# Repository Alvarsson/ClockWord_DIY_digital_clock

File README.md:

# ClockWork_DIY_digital_clock
Code for homemade digital clock. 

# Effects to add
"Circle" + line in the middle
Fill in/out on number change
"Circle" wave

# Important notes
The KiCad design doesn't have a voltage divider for the TX pin of the ESP8266. If the arduino isn't talking to the ESP8266 properly, make sure that the input voltage to the Arduino isn't too high.

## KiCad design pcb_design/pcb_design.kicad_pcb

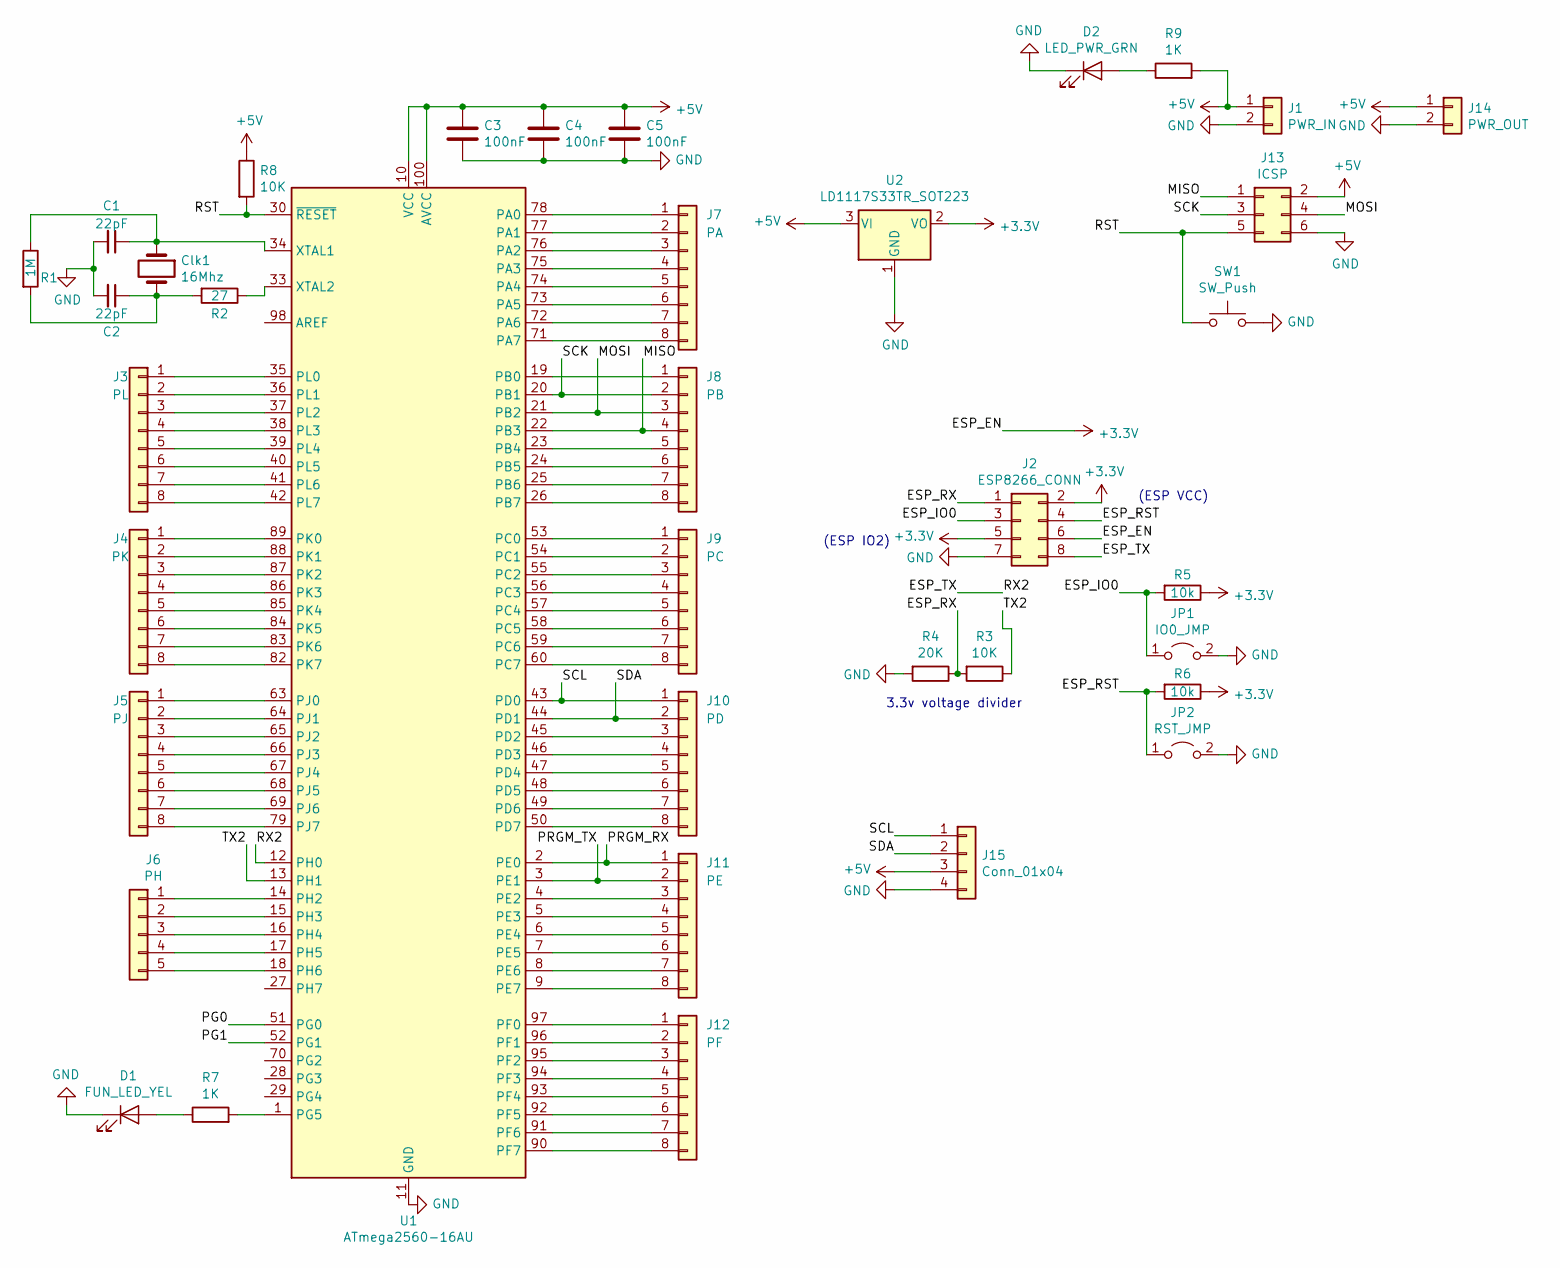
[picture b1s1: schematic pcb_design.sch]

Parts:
C1, C2: 22pF; C_0603_1608Metric
C3, C4, C5: 100nF; C_0603_1608Metric
Clk1: 16Mhz; Crystal_HC49-4H_Vertical
D1: FUN_LED_YEL; LED_0603_1608Metric
D2: LED_PWR_GRN; LED_0603_1608Metric
J1: PWR_IN; PinHeader_1x02_P2.54mm_Vertical
J2: ESP8266_CONN; PinHeader_2x04_P2.54mm_Vertical
J3: PL; PinHeader_1x08_P2.54mm_Vertical
J4: PK; PinHeader_1x08_P2.54mm_Vertical
J5: PJ; PinHeader_1x08_P2.54mm_Vertical
J6: PH; PinHeader_1x05_P2.54mm_Vertical
J7: PA; PinHeader_1x08_P2.54mm_Vertical
J8: PB; PinHeader_1x08_P2.54mm_Vertical
J9: PC; PinHeader_1x08_P2.54mm_Vertical
J10: PD; PinHeader_1x08_P2.54mm_Vertical
J11: PE; PinHeader_1x08_P2.54mm_Vertical
J12: PF; PinHeader_1x08_P2.54mm_Vertical
J13: ICSP; PinHeader_2x03_P2.54mm_Vertical
J14: PWR_OUT; PinHeader_1x02_P2.54mm_Vertical
J15: Conn_01x04; PinSocket_1x04_P2.54mm_Vertical
JP1: IO0_JMP; PinHeader_1x02_P2.54mm_Vertical
JP2: RST_JMP; PinHeader_1x02_P2.54mm_Vertical
R1: 1M; R_0603_1608Metric
R2: 27; R_0603_1608Metric
R3, R8: 10K; R_0603_1608Metric
R4: 20K; R_0603_1608Metric
R5, R6: 10k; R_0603_1608Metric
R7, R9: 1K; R_0603_1608Metric
SW1: SW_Push; SW_SPST_B3U-1000P
U1: ATmega2560-16AU; TQFP-100_14x14mm_P0.5mm
U2: LD1117S33TR_SOT223; SOT-223-3_TabPin2

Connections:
+3V3: J2.2, J2.5, J2.6, R5.1, R6.1, U2.2 (VO)
+5V: C3.1, C4.1, C5.1, J1.1, J13.2, J14.1, J15.3, R8.1, R9.2, U1.10 (VCC), U1.31 (VCC), U1.61 (VCC), U1.80 (VCC), U1.100 (AVCC), U2.3 (VI)
/ESP_IO0: J2.3, JP1.1 (A), R5.2
/ESP_RST: J2.4, JP2.1 (A), R6.2
/ESP_RX: J2.1, R3.2, R4.1
/ESP_TX: J2.8, U1.12 (PH0)
/MISO: J8.4, J13.1, U1.22 (PB3)
/MOSI: J8.3, J13.4, U1.21 (PB2)
/PG0: U1.51 (PG0)
/PG1: U1.52 (PG1)
/PRGM_RX: J11.1, U1.2 (PE0)
/PRGM_TX: J11.2, U1.3 (PE1)
/RST: J13.5, R8.2, SW1.1, U1.30 (~RESET)
/SCK: J8.2, J13.3, U1.20 (PB1)
/SCL: J10.1, J15.1, U1.43 (PD0)
/SDA: J10.2, J15.2, U1.44 (PD1)
/TX2: R3.1, U1.13 (PH1)
GND: C1.2, C2.2, C3.2, C4.2, C5.2, D1.1 (K), D2.1 (K), J1.2, J2.7, J13.6, J14.2, J15.4, JP1.2 (B), JP2.2 (B), R4.2, SW1.2, U1.11 (GND), U1.32 (GND), U1.62 (GND), U1.81 (GND), U1.99 (GND), U2.1 (GND)
unnamed: C1.1, Clk1.1, R1.1, U1.34 (XTAL1)
unnamed: C2.1, Clk1.2, R1.2, R2.2
unnamed: D1.2 (A), R7.1
unnamed: D2.2 (A), R9.1
unnamed: J3.1, U1.35 (PL0)
unnamed: J3.2, U1.36 (PL1)
unnamed: J3.3, U1.37 (PL2)
unnamed: J3.4, U1.38 (PL3)
unnamed: J3.5, U1.39 (PL4)
unnamed: J3.6, U1.40 (PL5)
unnamed: J3.7, U1.41 (PL6)
unnamed: J3.8, U1.42 (PL7)
unnamed: J4.1, U1.89 (PK0)
unnamed: J4.2, U1.88 (PK1)
unnamed: J4.3, U1.87 (PK2)
unnamed: J4.4, U1.86 (PK3)
unnamed: J4.5, U1.85 (PK4)
unnamed: J4.6, U1.84 (PK5)
unnamed: J4.7, U1.83 (PK6)
unnamed: J4.8, U1.82 (PK7)
unnamed: J5.1, U1.63 (PJ0)
unnamed: J5.2, U1.64 (PJ1)
unnamed: J5.3, U1.65 (PJ2)
unnamed: J5.4, U1.66 (PJ3)
unnamed: J5.5, U1.67 (PJ4)
unnamed: J5.6, U1.68 (PJ5)
unnamed: J5.7, U1.69 (PJ6)
unnamed: J5.8, U1.79 (PJ7)
unnamed: J6.1, U1.14 (PH2)
unnamed: J6.2, U1.15 (PH3)
unnamed: J6.3, U1.16 (PH4)
unnamed: J6.4, U1.17 (PH5)
unnamed: J6.5, U1.18 (PH6)
unnamed: J7.1, U1.78 (PA0)
unnamed: J7.2, U1.77 (PA1)
unnamed: J7.3, U1.76 (PA2)
unnamed: J7.4, U1.75 (PA3)
unnamed: J7.5, U1.74 (PA4)
unnamed: J7.6, U1.73 (PA5)
unnamed: J7.7, U1.72 (PA6)
unnamed: J7.8, U1.71 (PA7)
unnamed: J8.1, U1.19 (PB0)
unnamed: J8.5, U1.23 (PB4)
unnamed: J8.6, U1.24 (PB5)
unnamed: J8.7, U1.25 (PB6)
unnamed: J8.8, U1.26 (PB7)
unnamed: J9.1, U1.53 (PC0)
unnamed: J9.2, U1.54 (PC1)
unnamed: J9.3, U1.55 (PC2)
unnamed: J9.4, U1.56 (PC3)
unnamed: J9.5, U1.57 (PC4)
unnamed: J9.6, U1.58 (PC5)
unnamed: J9.7, U1.59 (PC6)
unnamed: J9.8, U1.60 (PC7)
unnamed: J10.3, U1.45 (PD2)
unnamed: J10.4, U1.46 (PD3)
unnamed: J10.5, U1.47 (PD4)
unnamed: J10.6, U1.48 (PD5)
unnamed: J10.7, U1.49 (PD6)
unnamed: J10.8, U1.50 (PD7)
unnamed: J11.3, U1.4 (PE2)
unnamed: J11.4, U1.5 (PE3)
unnamed: J11.5, U1.6 (PE4)
unnamed: J11.6, U1.7 (PE5)
unnamed: J11.7, U1.8 (PE6)
unnamed: J11.8, U1.9 (PE7)
unnamed: J12.1, U1.97 (PF0)
unnamed: J12.2, U1.96 (PF1)
unnamed: J12.3, U1.95 (PF2)
unnamed: J12.4, U1.94 (PF3)
unnamed: J12.5, U1.93 (PF4)
unnamed: J12.6, U1.92 (PF5)
unnamed: J12.7, U1.91 (PF6)
unnamed: J12.8, U1.90 (PF7)
unnamed: R2.1, U1.33 (XTAL2)
unnamed: R7.2, U1.1 (PG5)

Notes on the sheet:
(ESP VCC)
(ESP IO2)
3.3v voltage divider

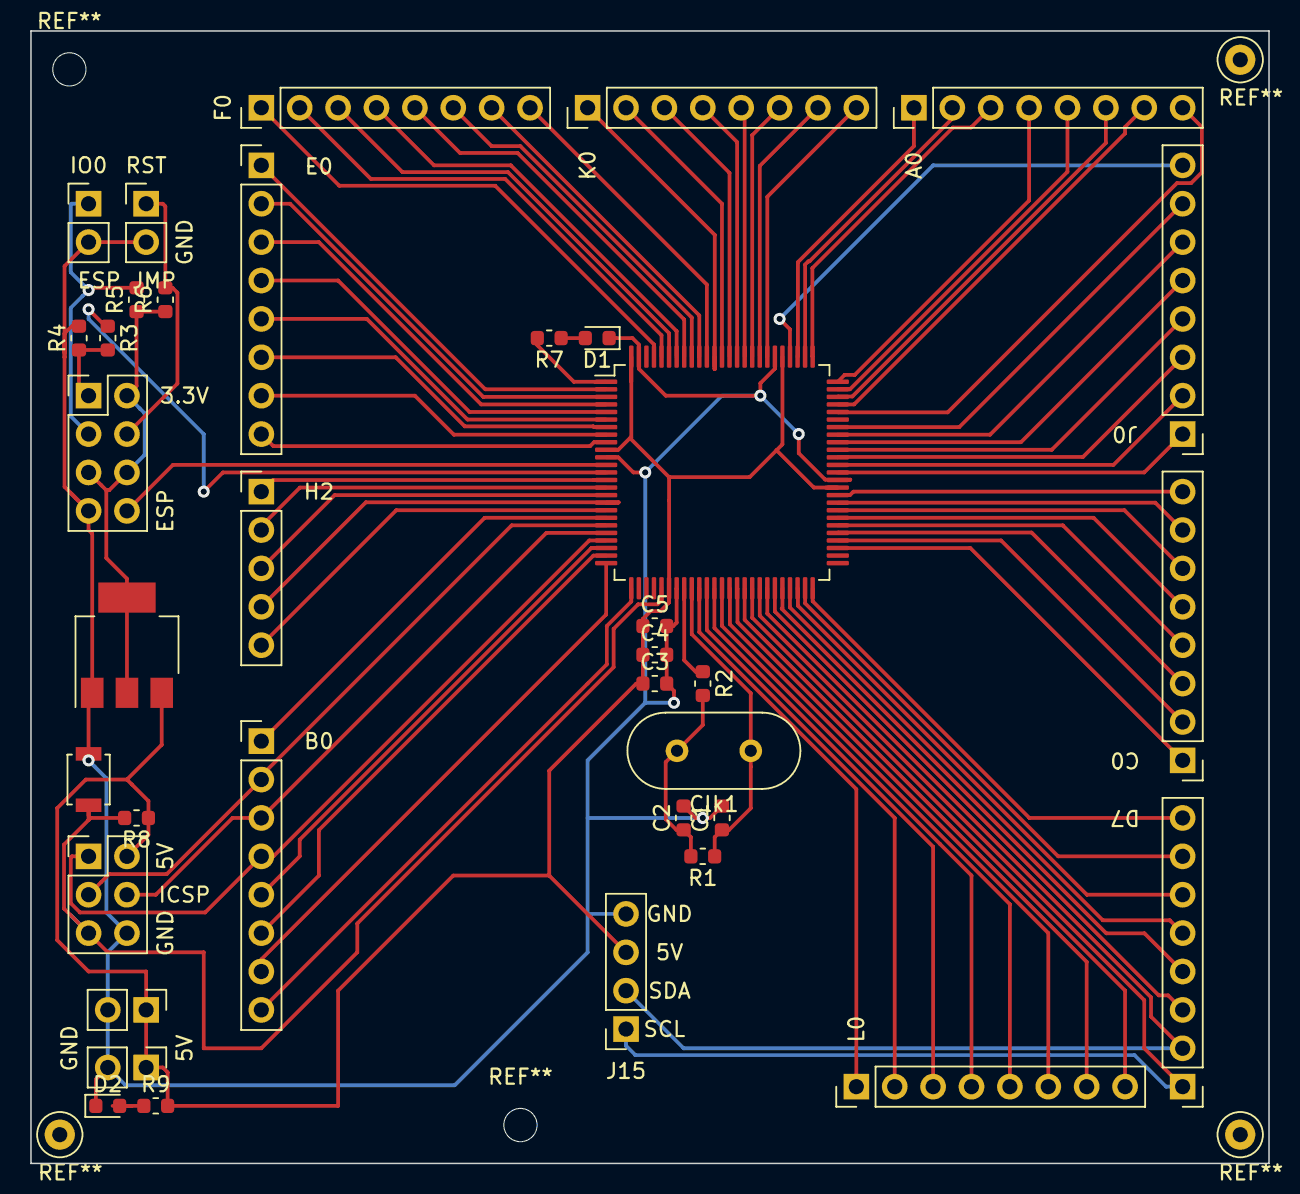
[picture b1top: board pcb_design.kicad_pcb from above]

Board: 2 copper layers, 81.9 x 74.9 mm, 37 parts (0 on the bottom side), 92 nets.

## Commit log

2021-04-01 Add clock controller
2021-04-01 Display time osv
2021-04-04 With working ESP and stuff
2021-04-04 Important comment
2021-04-04 added rainbow
2021-04-04 Fix functions a bit more
2021-04-04 Column shiz
2021-04-04 Move around and fix names
2021-04-04 Add names
2021-04-04 Add rgb wave function
2021-04-05 Try using uint16_t instead of floats
2021-04-05 Rainbow animation! (Sort of)
2021-04-05 Working waves
2021-04-05 Rainbow clock!
2021-04-05 Move definition/declaration
2021-04-05 Practically functional clock
2021-04-06 Add kicad files
2021-04-06 Damn this is cool
2021-04-07 Fix 9
2021-04-07 Add small thingoes
2021-04-07 Move and stuff
2021-04-08 Add ISP header and bit more of USB thingo
2021-04-08 Move around
2021-04-09 Make PCB design
2021-04-10 Almost done?
2021-04-10 Small changes
2021-04-10 Add some effects to add
2021-04-16 Circle wave
2021-04-16 Split out some stuff
2021-04-16 Only 1 error message!
2021-04-17 Add DS3231 RTC header
2021-04-17 Add lineout to PCB design
2021-04-17 Weird shit
2021-04-17 Fix design issues
2021-04-17 Use correctly sized crystal, more changes
2021-04-17 Reworking
2021-04-17 Add mounting holes
2021-04-17 Ignore useless files
2021-04-20 Yes euh idk
2021-04-20 Refactoring
2021-05-24 0603EU -> 0603US
2021-07-25 Use interrupt instead of timeout More stuff
2021-07-25 Update for atmega2560 board
2021-07-25 Read the time and display it on the screen
2021-07-27 Actually working now
2021-07-31 Add some more special effects
    Try to add a watchdog for reading the time so it's less likely to get stuck
2021-12-02 Update to different serial port (for new cool kard) and timezone
2022-10-25 New pin numbers
2022-10-25 Update to new, soldered pins
    Change timezone
2022-11-10 Update to winter time
